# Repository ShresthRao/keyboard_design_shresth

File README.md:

# shresth_macropad

## BOM

Seeed XIAO RP2040
MX-style switches (12x)

1N4148 diodes

EC11 rotary encoder

0.91" OLED display (SSD1306)

Keycaps (12x)

Custom PCB

Case (Top)

Case (Bottom)

Screws

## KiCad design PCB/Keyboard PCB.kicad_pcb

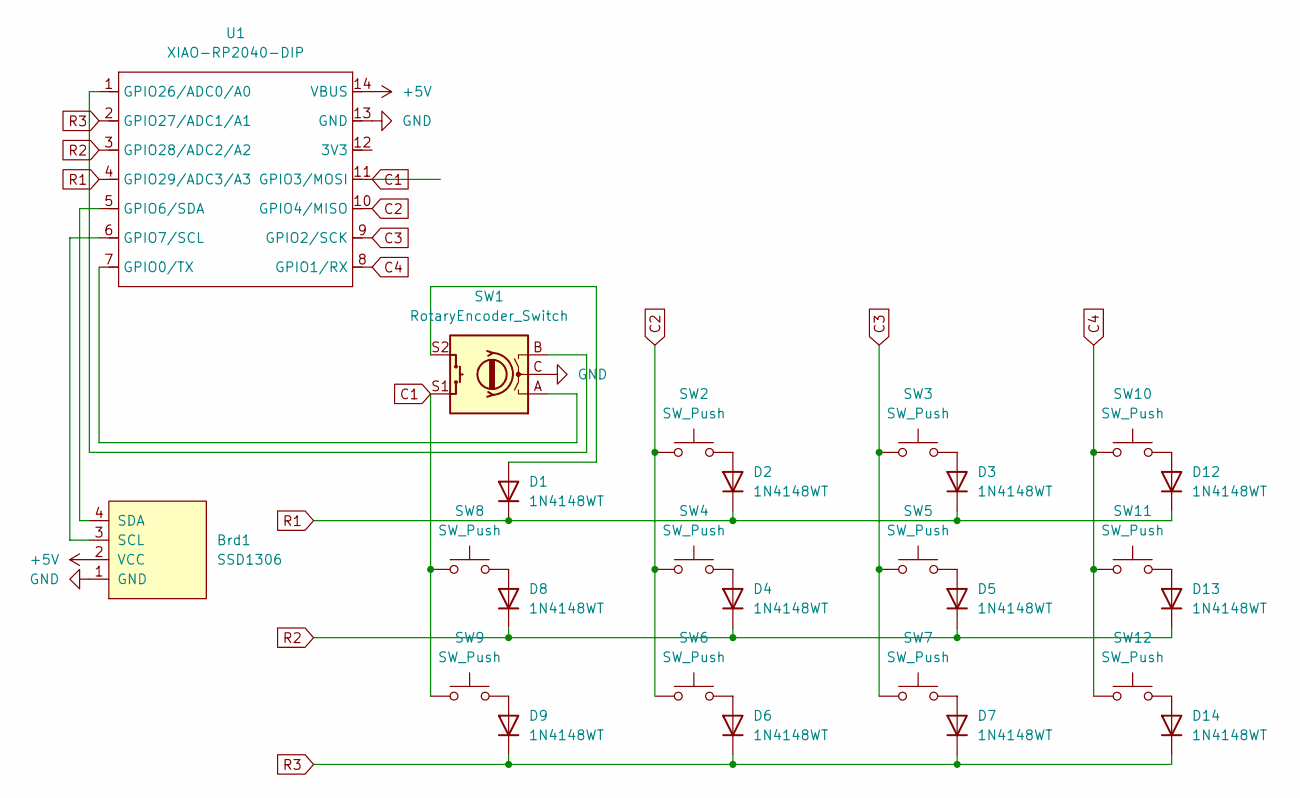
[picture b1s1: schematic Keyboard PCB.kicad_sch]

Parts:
Brd1: SSD1306; SSD1306-0.91-OLED-4pin-128x32
D1, D2, D3, D4, D5, D6, D7, D8, D9, D12, D13, D14: 1N4148WT; D_SOD-523
SW1: RotaryEncoder_Switch; RotaryEncoder_Alps_EC11E-Switch_Vertical_H20mm
SW2, SW3, SW4, SW5, SW6, SW7, SW8, SW9, SW10: SW_Push; SW_Cherry_MX_1.00u_PCB
SW11, SW12: SW_Push; SW_Cherry_MX_1.00u_Plate
U1: XIAO-RP2040-DIP

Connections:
+5V: Brd1.2 (VCC), U1.14 (VBUS)
C1: SW1.S1, SW8.1, SW9.1, U1.11 (GPIO3/MOSI)
C2: SW2.1, SW4.1, SW6.1, U1.10 (GPIO4/MISO)
C3: SW3.1, SW5.1, SW7.1, U1.9 (GPIO2/SCK)
C4: SW10.1, SW11.1, SW12.1, U1.8 (GPIO1/RX)
GND: Brd1.1 (GND), SW1.C, U1.13 (GND)
unnamed: Brd1.3 (SCL), U1.6 (GPIO7/SCL)
unnamed: Brd1.4 (SDA), U1.5 (GPIO6/SDA)
unnamed: D1.2 (A), SW1.S2
unnamed: D2.2 (A), SW2.2
unnamed: D3.2 (A), SW3.2
unnamed: D4.2 (A), SW4.2
unnamed: D5.2 (A), SW5.2
unnamed: D6.2 (A), SW6.2
unnamed: D7.2 (A), SW7.2
unnamed: D8.2 (A), SW8.2
unnamed: D9.2 (A), SW9.2
unnamed: D12.2 (A), SW10.2
unnamed: D13.2 (A), SW11.2
unnamed: D14.2 (A), SW12.2
unnamed: SW1.A, U1.7 (GPIO0/TX)
unnamed: SW1.B, U1.1 (GPIO26/ADC0/A0)
R1: D1.1 (K), D2.1 (K), D3.1 (K), D12.1 (K), U1.4 (GPIO29/ADC3/A3)
R2: D4.1 (K), D5.1 (K), D8.1 (K), D13.1 (K), U1.3 (GPIO28/ADC2/A2)
R3: D6.1 (K), D7.1 (K), D9.1 (K), D14.1 (K), U1.2 (GPIO27/ADC1/A1)

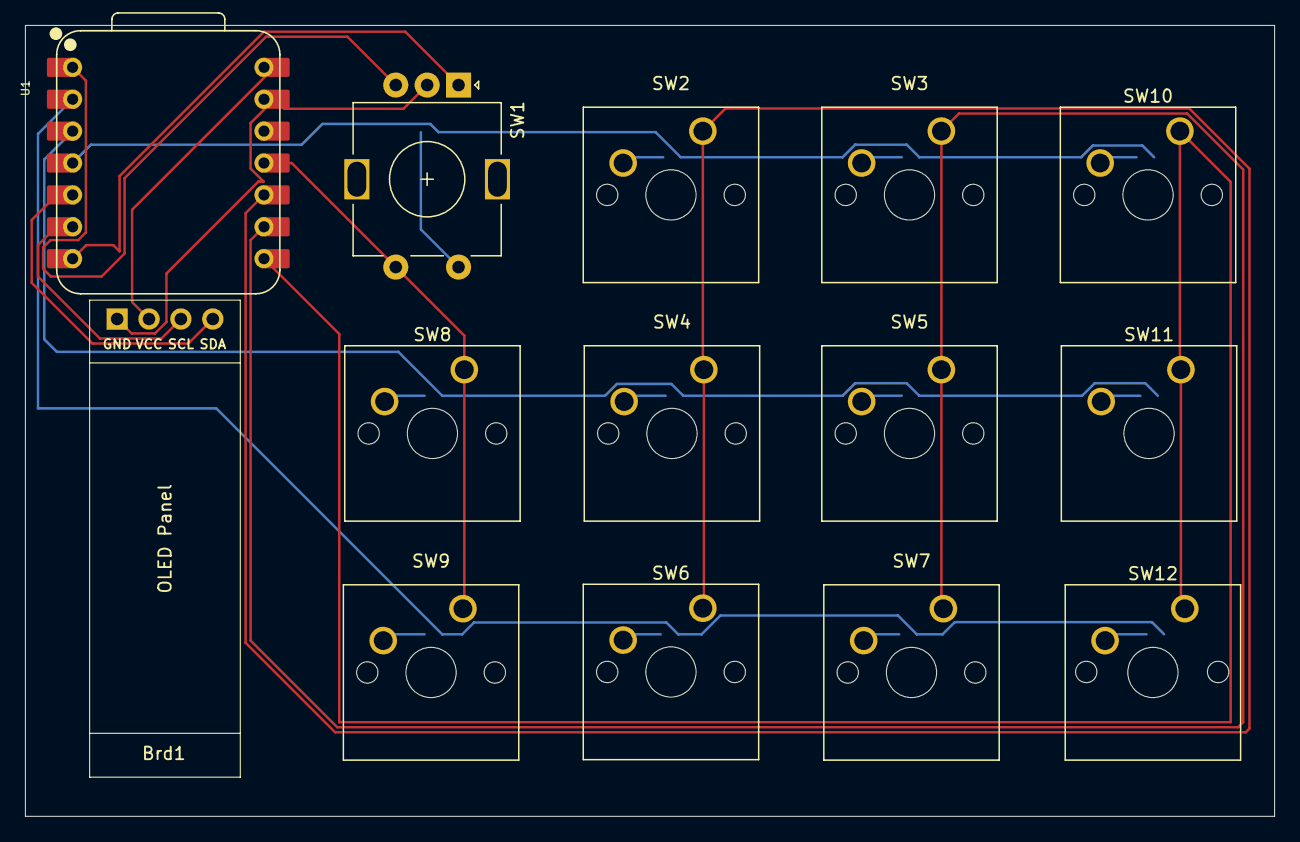
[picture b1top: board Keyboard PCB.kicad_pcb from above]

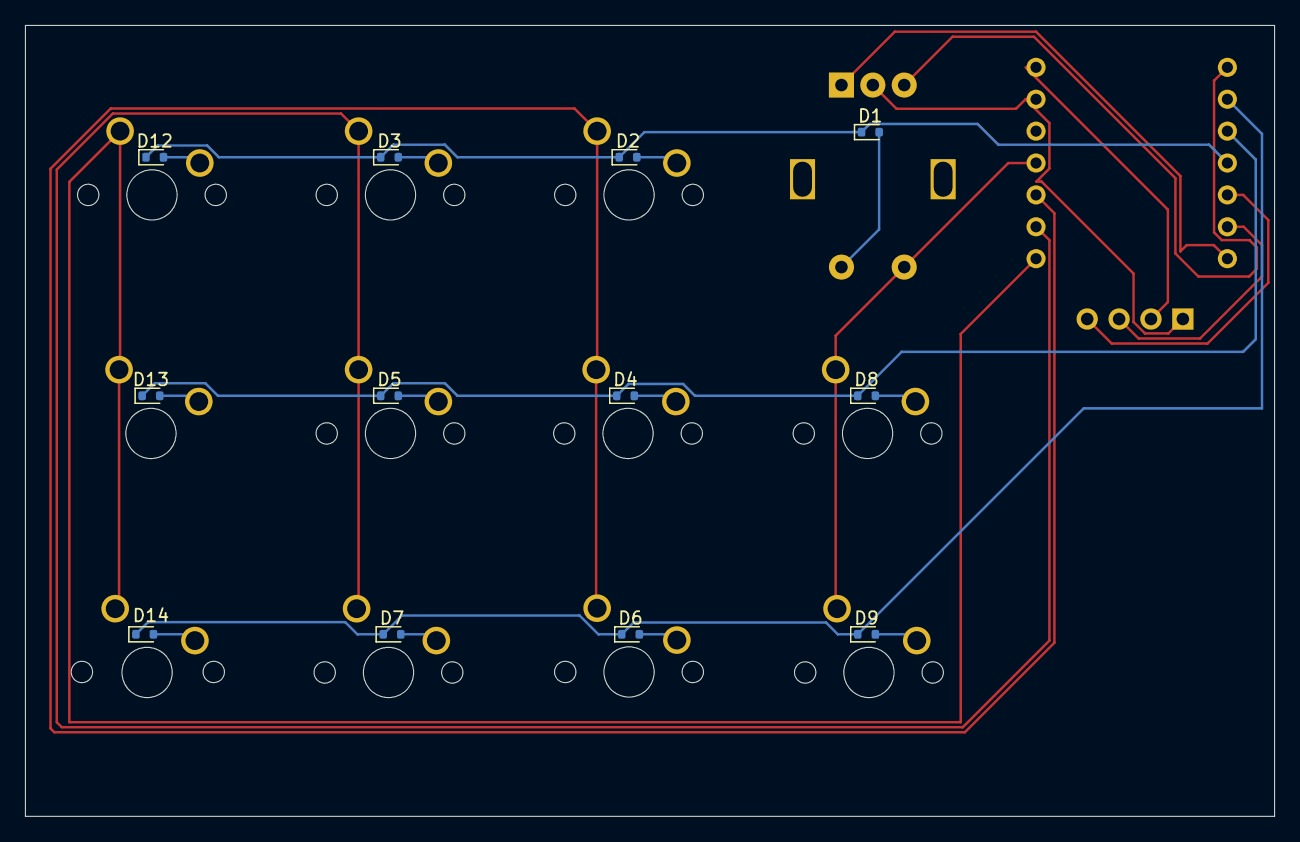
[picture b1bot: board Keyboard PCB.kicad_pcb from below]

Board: 2 copper layers, 99.5 x 63.0 mm, 26 parts (12 on the bottom side), 25 nets.

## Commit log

2026-03-29 Add files via upload
    These are the files related to my Hack Club - Macropad project
2026-03-29 Add files via upload
    These are the files of my Hack Club - Macropad project, it is a 3 X 4 grid keyboard with 12 switches.
2026-03-29 Add files via upload
    This is the readme.md file
2026-03-29 Add files via upload
    readme.md for firmwares
2026-03-29 Add files via upload
    Assets (images)
